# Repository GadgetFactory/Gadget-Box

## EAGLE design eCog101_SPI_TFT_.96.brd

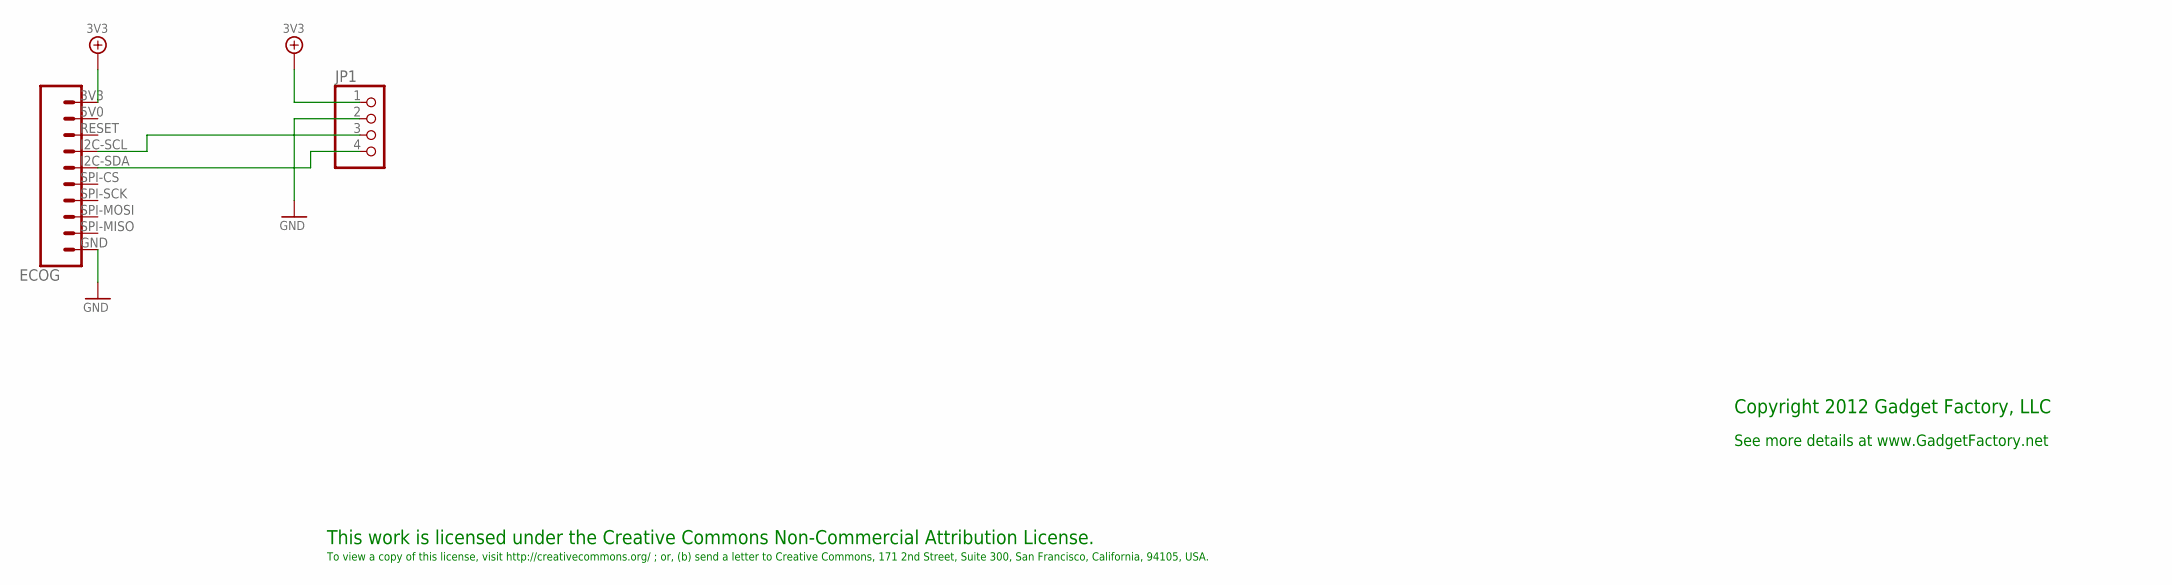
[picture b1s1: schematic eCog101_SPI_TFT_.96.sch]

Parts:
ECOG: ECOG_BUSES_ROWECOG_BUSES_SMD; ECOG_BUSES_SMD
JP1: PINHD-1X4; 1X04

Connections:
3V3: ECOG.3V3, JP1.1
GND: ECOG.GND, JP1.2
unnamed: ECOG.I2C-SCL, JP1.3
unnamed: ECOG.I2C-SDA, JP1.4

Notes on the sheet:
This work is licensed under the Creative Commons Non-Commercial Attribution License.
To view a copy of this license, visit http://creativecommons.org/ ; or, (b) send a letter to Creative Commons, 171 2nd Street, Suite 300, San Francisco, California, 94105, USA.
Copyright 2012 Gadget Factory, LLC
See more details at www.GadgetFactory.net

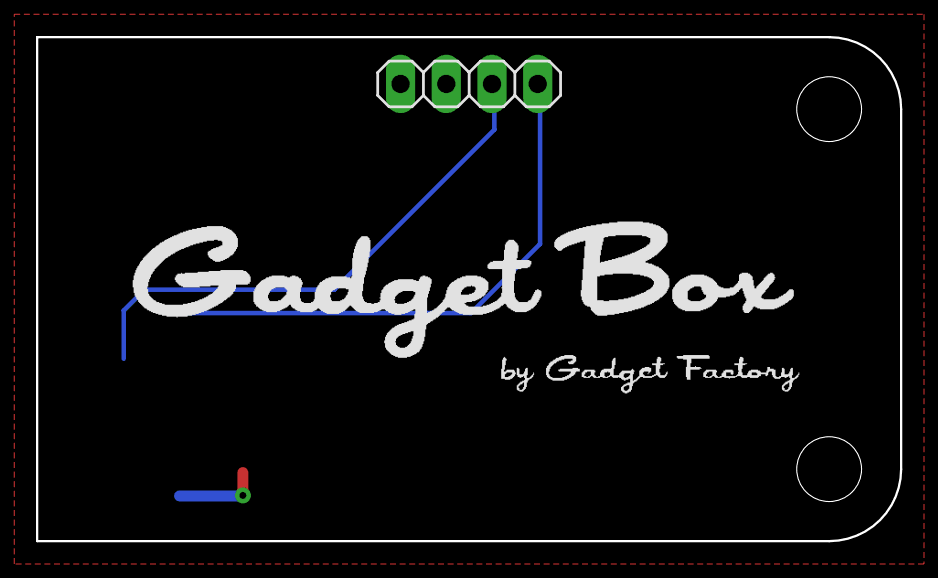
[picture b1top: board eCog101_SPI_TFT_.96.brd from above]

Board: 2 copper layers, 48.0 x 28.0 mm, 3 parts (0 on the bottom side), 4 nets.

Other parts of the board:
U$1: GADGETBOX_TEXT

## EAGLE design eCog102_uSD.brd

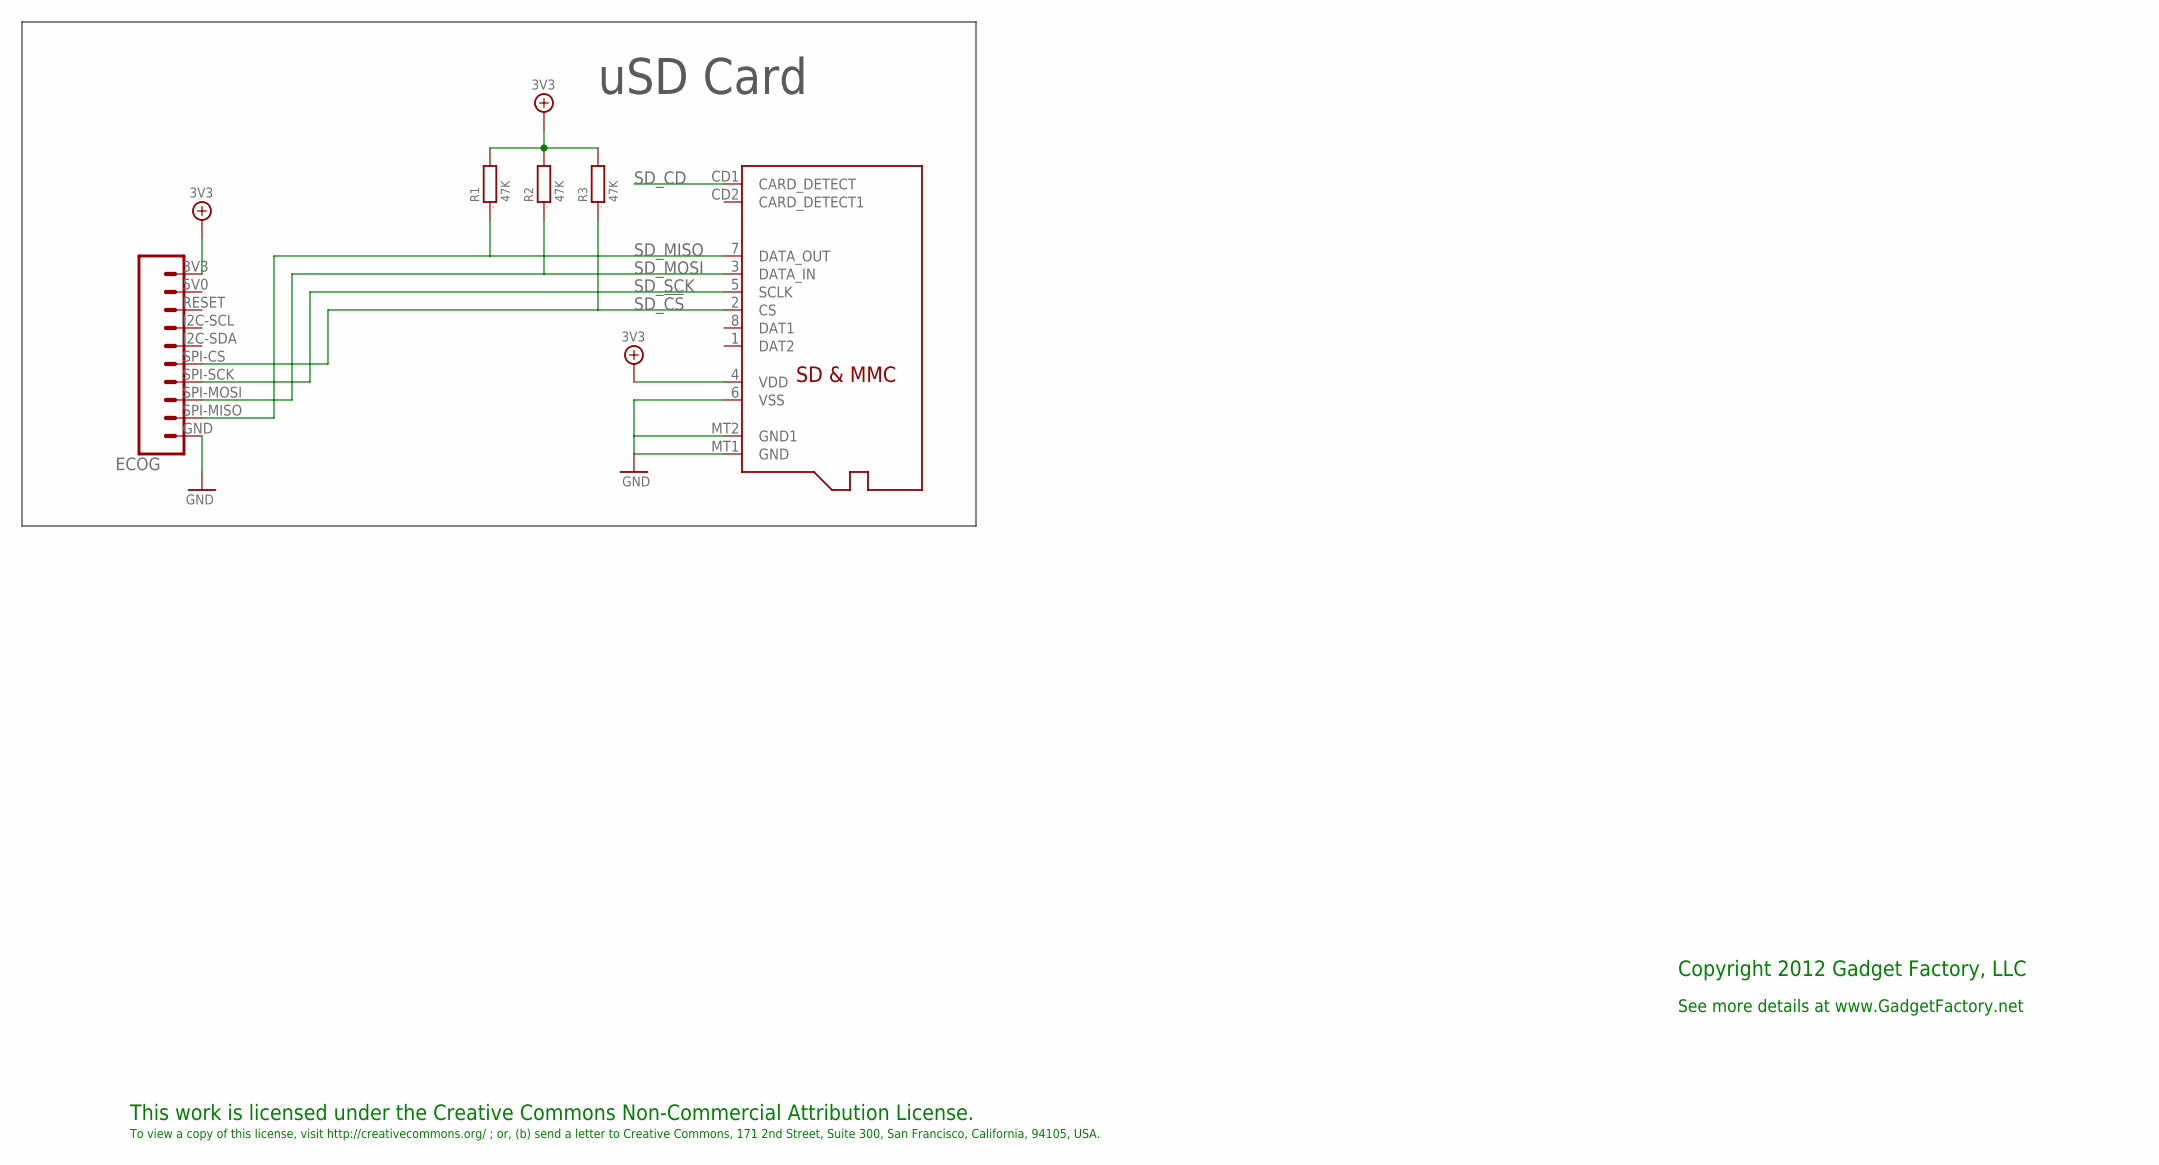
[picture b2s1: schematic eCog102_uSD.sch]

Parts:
ECOG: ECOG_BUSES_ROWECOG_BUSES_SMD; ECOG_BUSES_SMD
R1, R2, R3: 47K; 0805; PARTNO RMCF0805JT47K0; DIGIKEY RMCF0805JT47K0CT-ND
SD1: MICROSD; PARTNO 101-00660-68-6; DIGIKEY 101-00660-68-6-1-ND

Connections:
3V3: ECOG.3V3, R1.2, R2.2, R3.2, SD1.4 (VDD)
GND: ECOG.GND, SD1.6 (VSS), SD1.MT1 (GND), SD1.MT2 (GND1)
SD_!CS: ECOG.SPI-CS, R3.1, SD1.2 (CS)
SD_CD: SD1.CD1 (CARD_DETECT)
SD_MISO: ECOG.SPI-MISO, R1.1, SD1.7 (DATA_OUT)
SD_MOSI: ECOG.SPI-MOSI, R2.1, SD1.3 (DATA_IN)
SD_SCK: ECOG.SPI-SCK, SD1.5 (SCLK)

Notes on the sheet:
This work is licensed under the Creative Commons Non-Commercial Attribution License.
To view a copy of this license, visit http://creativecommons.org/ ; or, (b) send a letter to Creative Commons, 171 2nd Street, Suite 300, San Francisco, California, 94105, USA.
Copyright 2012 Gadget Factory, LLC
See more details at www.GadgetFactory.net
uSD Card

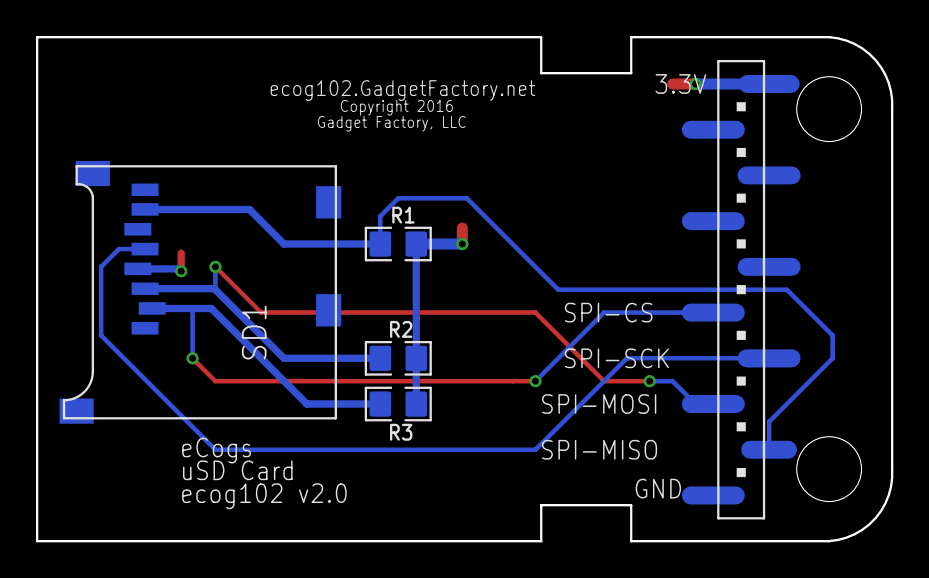
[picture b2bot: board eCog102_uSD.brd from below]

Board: 2 copper layers, 47.5 x 28.0 mm, 7 parts (4 on the bottom side), 6 nets.

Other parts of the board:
U$1: GADGETBOX_TEXT
U$2: OSHW_FILLX200_NOTEXT

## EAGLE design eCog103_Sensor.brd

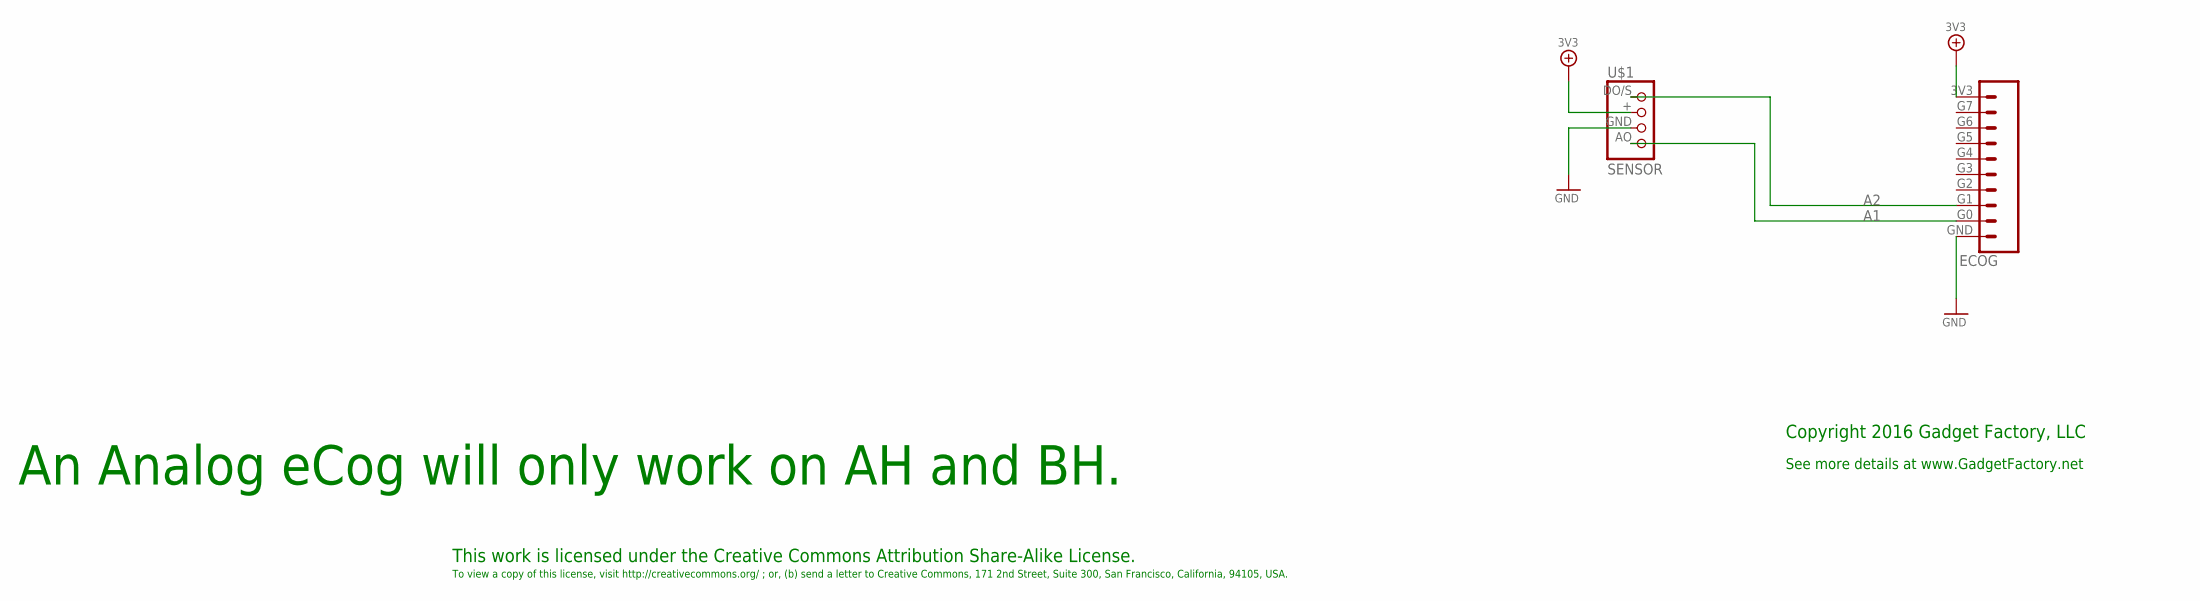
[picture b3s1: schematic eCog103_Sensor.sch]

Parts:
ECOG: ECOG_GENERAL_ROWECOG_GENERAL_SMD; ECOG_GENERAL_SMD
U$1: SENSOR; SENSOR-HJX4

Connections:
3V3: ECOG.3V3, U$1.+
A1: ECOG.G0, U$1.AO
A2: ECOG.G1, U$1.DO/S
GND: ECOG.GND, U$1.GND

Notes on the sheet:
This work is licensed under the Creative Commons Attribution Share-Alike License.
To view a copy of this license, visit http://creativecommons.org/ ; or, (b) send a letter to Creative Commons, 171 2nd Street, Suite 300, San Francisco, California, 94105, USA.
Copyright 2016 Gadget Factory, LLC
See more details at www.GadgetFactory.net
An Analog eCog will only work on AH and BH.

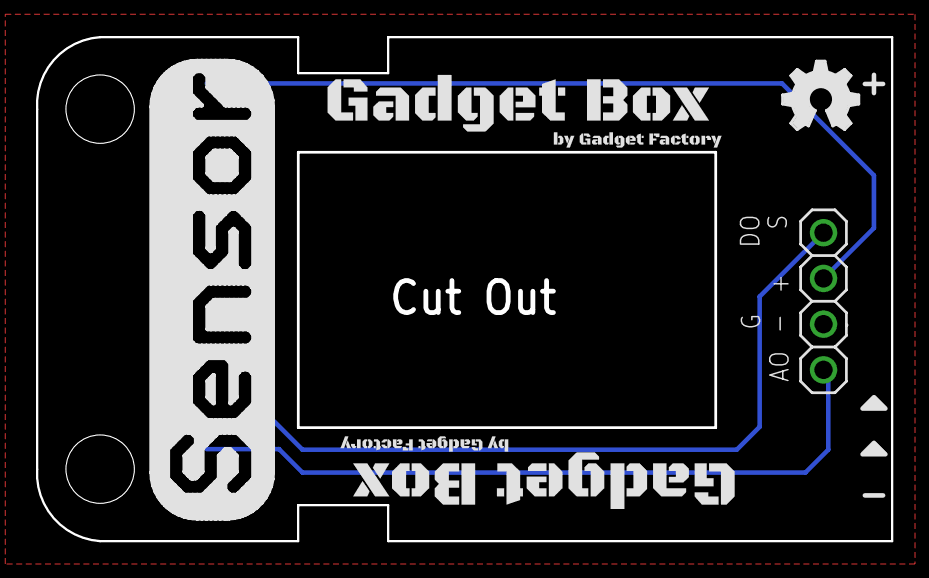
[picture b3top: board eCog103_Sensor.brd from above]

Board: 2 copper layers, 47.5 x 28.0 mm, 7 parts (0 on the bottom side), 4 nets.

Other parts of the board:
U$2, U$3: LEGEND_ANALOG
U$4, U$6: GADGETBOX_SMALL
U$5: OSHW_FILLX150_NOTEXT

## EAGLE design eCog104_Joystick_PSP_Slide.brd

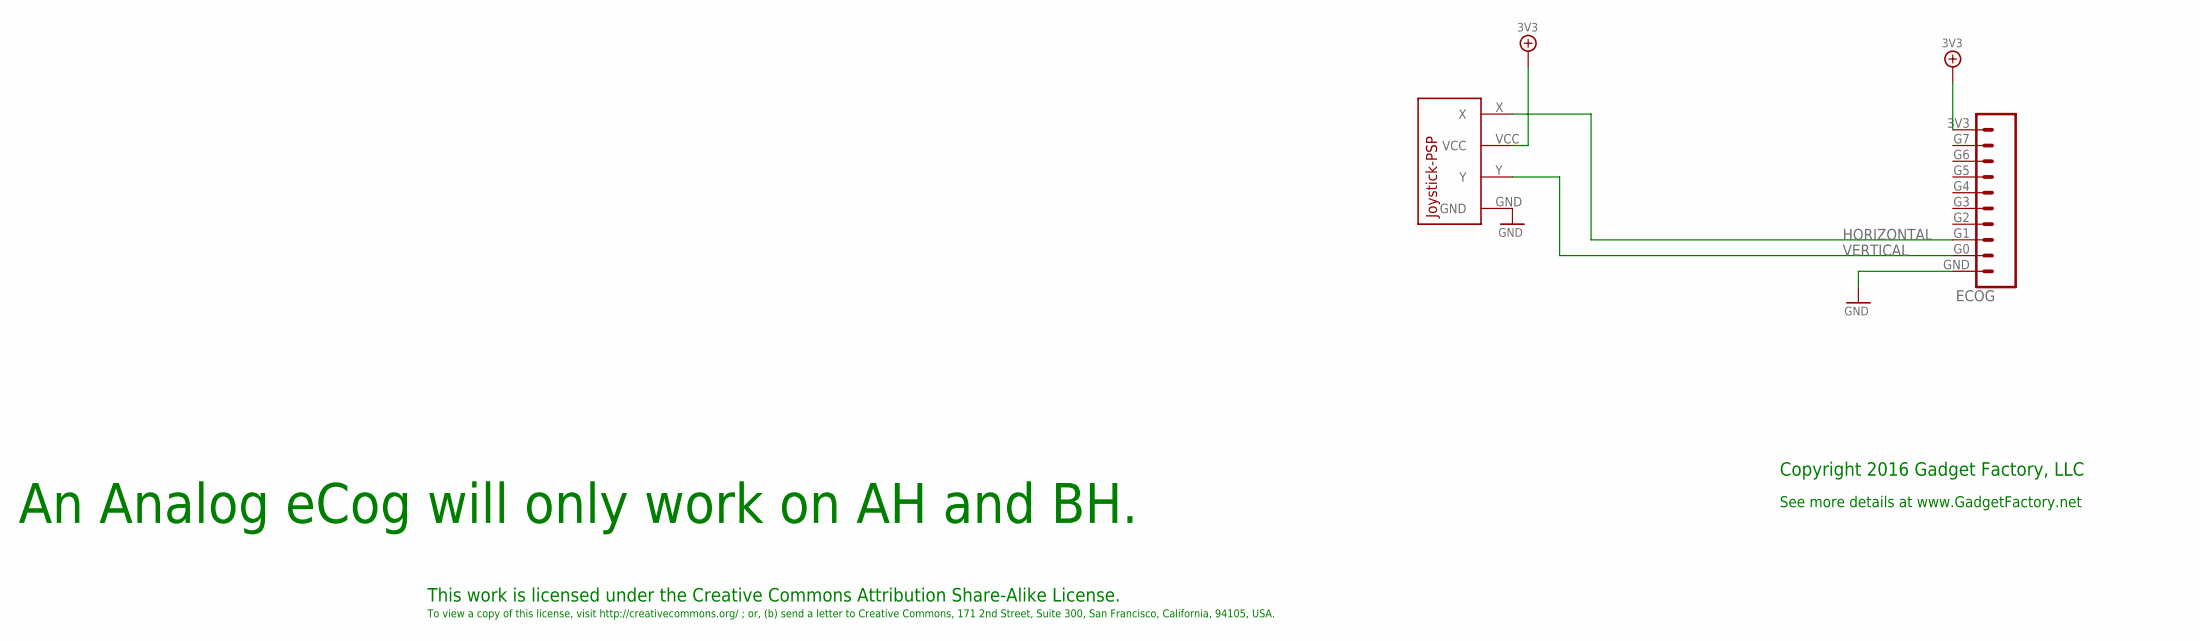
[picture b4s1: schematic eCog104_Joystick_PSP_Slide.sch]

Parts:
ECOG: ECOG_GENERAL_ROWECOG_GENERAL_SMD; ECOG_GENERAL_SMD
U$4: JOYSTICK-PSP1000

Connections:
3V3: ECOG.3V3, U$4.VCC
GND: ECOG.GND, U$4.GND
HORIZONTAL: ECOG.G1, U$4.X
VERTICAL: ECOG.G0, U$4.Y

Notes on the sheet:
This work is licensed under the Creative Commons Attribution Share-Alike License.
To view a copy of this license, visit http://creativecommons.org/ ; or, (b) send a letter to Creative Commons, 171 2nd Street, Suite 300, San Francisco, California, 94105, USA.
Copyright 2016 Gadget Factory, LLC
See more details at www.GadgetFactory.net
An Analog eCog will only work on AH and BH.

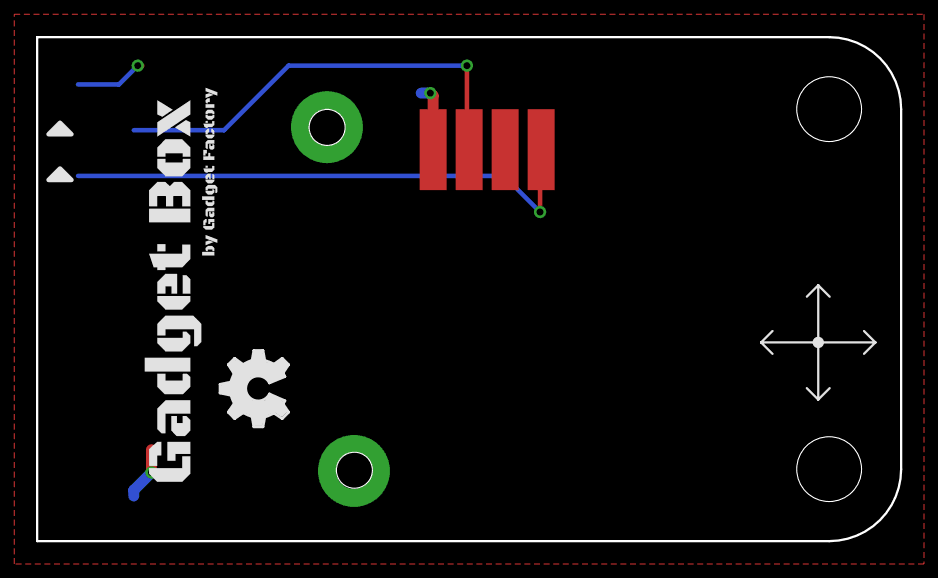
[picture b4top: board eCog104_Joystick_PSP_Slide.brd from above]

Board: 2 copper layers, 48.0 x 28.0 mm, 6 parts (0 on the bottom side), 4 nets.

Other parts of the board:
U$1, U$2: LEGEND_ANALOG
U$3: GADGETBOX_SMALL
U$5: OSHW_FILLX150_NOTEXT

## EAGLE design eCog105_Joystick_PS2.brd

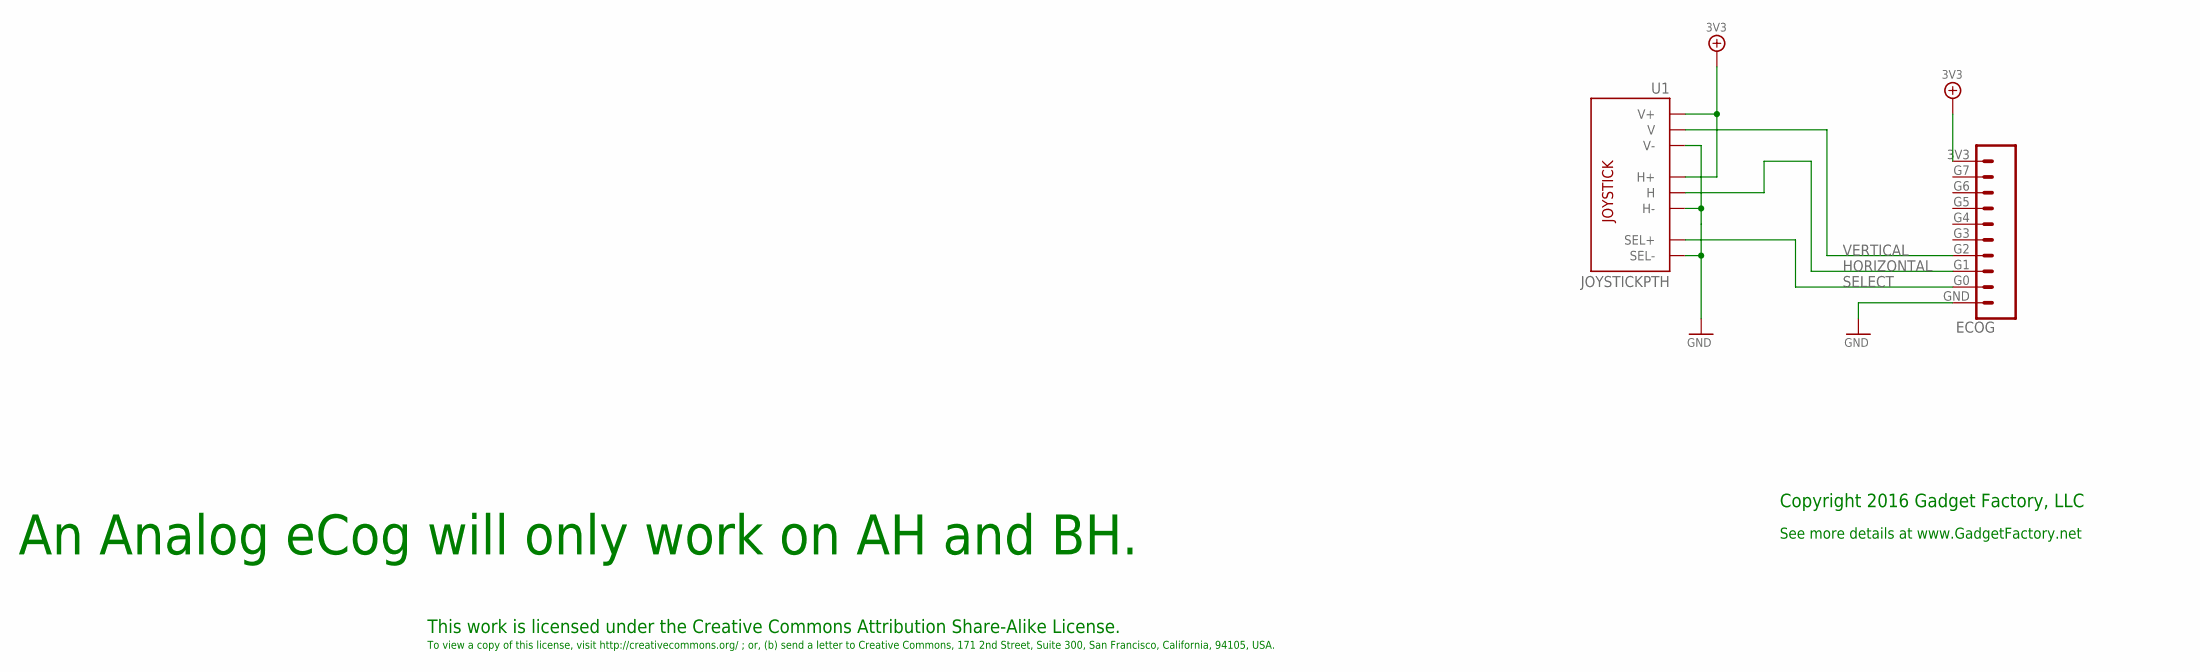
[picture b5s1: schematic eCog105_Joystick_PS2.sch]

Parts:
ECOG: ECOG_GENERAL_ROWECOG_GENERAL_SMD; ECOG_GENERAL_SMD
U1: JOYSTICKPTH; JOYSTICK

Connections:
3V3: ECOG.3V3, U1.H1 (H+), U1.V1 (V+)
GND: ECOG.GND, U1.B2A (SEL-), U1.H3 (H-), U1.V3 (V-)
HORIZONTAL: ECOG.G1, U1.H2 (H)
SELECT: ECOG.G0, U1.B1A (SEL+)
VERTICAL: ECOG.G2, U1.V2 (V)

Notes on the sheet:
This work is licensed under the Creative Commons Attribution Share-Alike License.
To view a copy of this license, visit http://creativecommons.org/ ; or, (b) send a letter to Creative Commons, 171 2nd Street, Suite 300, San Francisco, California, 94105, USA.
Copyright 2016 Gadget Factory, LLC
See more details at www.GadgetFactory.net
An Analog eCog will only work on AH and BH.

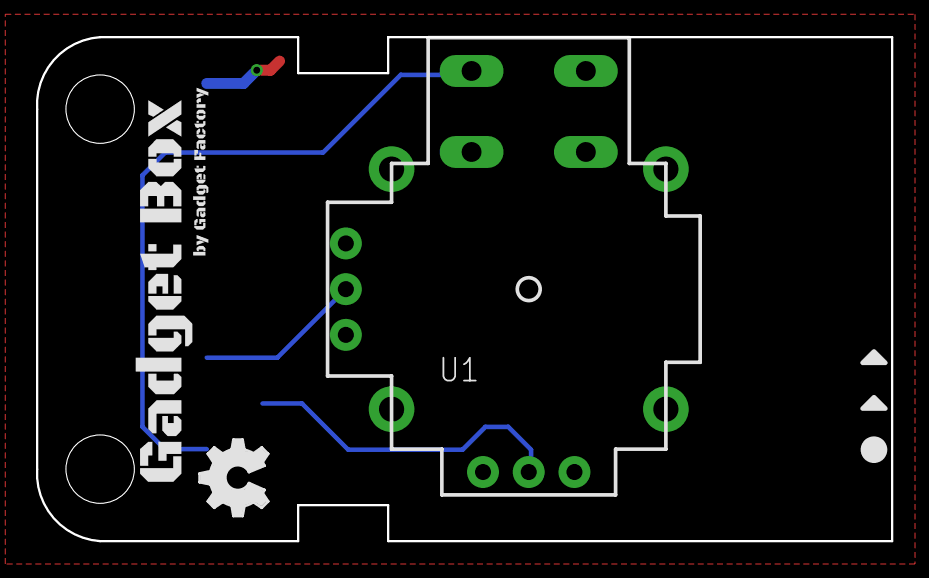
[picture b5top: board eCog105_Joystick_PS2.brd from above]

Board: 2 copper layers, 47.5 x 28.0 mm, 7 parts (0 on the bottom side), 5 nets.

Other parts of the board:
U$1, U$2: LEGEND_ANALOG
U$3: LEGEND_DIO
U$4: GADGETBOX_SMALL
U$5: OSHW_FILLX150_NOTEXT

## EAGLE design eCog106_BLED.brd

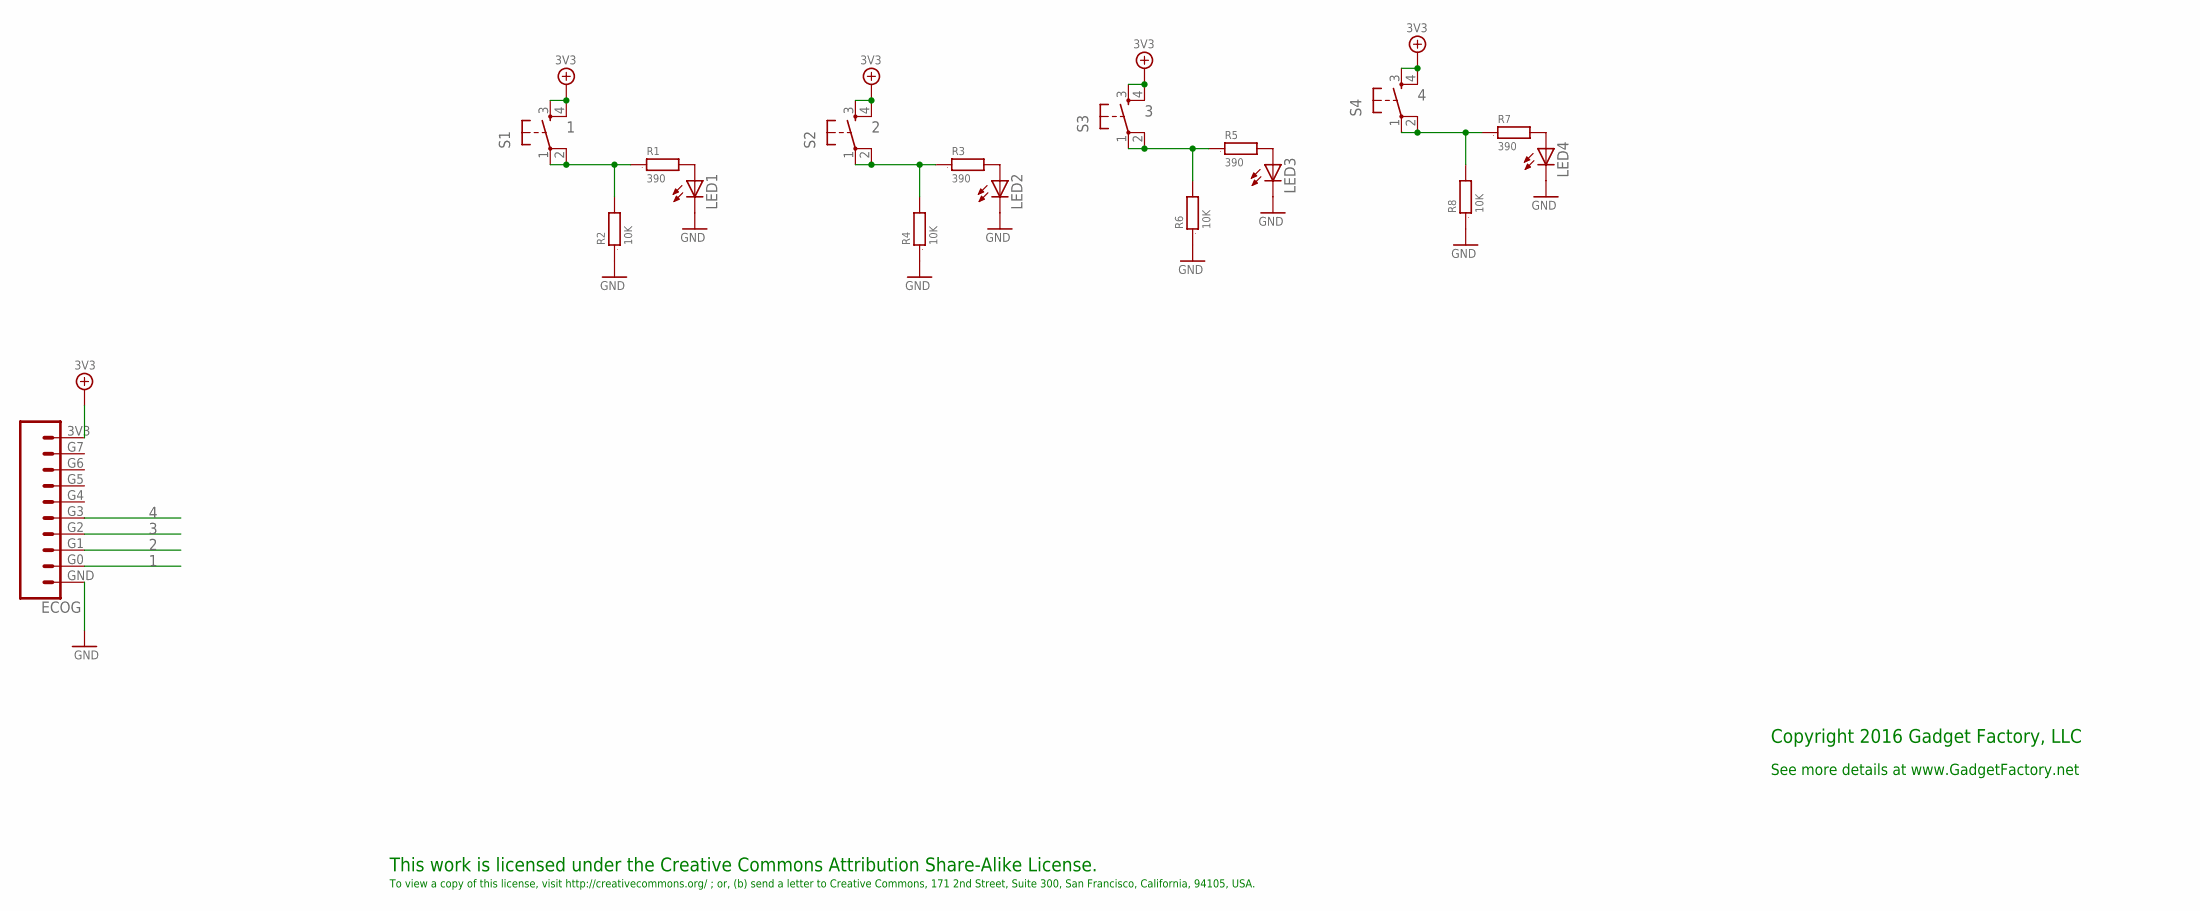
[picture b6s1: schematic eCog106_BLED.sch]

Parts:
ECOG: ECOG_GENERAL_ROWECOG_GENERAL_SMD; ECOG_GENERAL_SMD
LED1, LED2, LED3, LED4: LEDCHIP-LED0805; CHIP-LED0805; DIGIKEY 475-1410-2-ND
R1, R3, R5, R7: 390; 0805; DIGIKEY RMCF0805JT390RCT-ND
R2, R4, R6, R8: 10K; 0805; DIGIKEY RMCF0805JT10K0CT-ND
S1, S2, S3, S4: TAC_SWITCHPTH; TACTILE-PTH; DIGIKEY 679-2428-ND

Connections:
1: ECOG.G0, R1.1, R2.2, S1.1, S1.2
2: ECOG.G1, R3.1, R4.2, S2.1, S2.2
3: ECOG.G2, R5.1, R6.2, S3.1, S3.2
3V3: ECOG.3V3, S1.3, S1.4, S2.3, S2.4, S3.3, S3.4, S4.3, S4.4
4: ECOG.G3, R7.1, R8.2, S4.1, S4.2
GND: ECOG.GND, LED1.C, LED2.C, LED3.C, LED4.C, R2.1, R4.1, R6.1, R8.1
unnamed: LED1.A, R1.2
unnamed: LED2.A, R3.2
unnamed: LED3.A, R5.2
unnamed: LED4.A, R7.2

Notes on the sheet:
This work is licensed under the Creative Commons Attribution Share-Alike License.
To view a copy of this license, visit http://creativecommons.org/ ; or, (b) send a letter to Creative Commons, 171 2nd Street, Suite 300, San Francisco, California, 94105, USA.
Copyright 2016 Gadget Factory, LLC
See more details at www.GadgetFactory.net

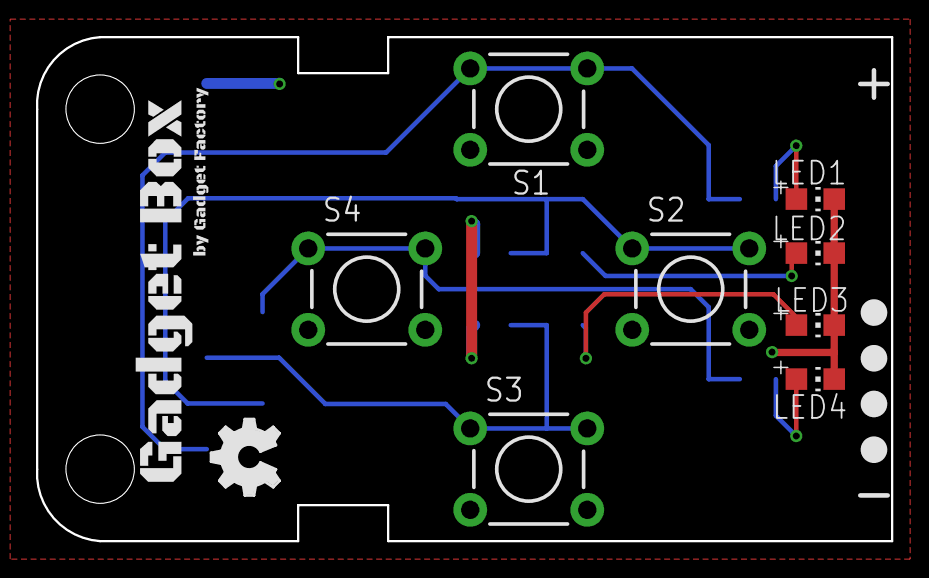
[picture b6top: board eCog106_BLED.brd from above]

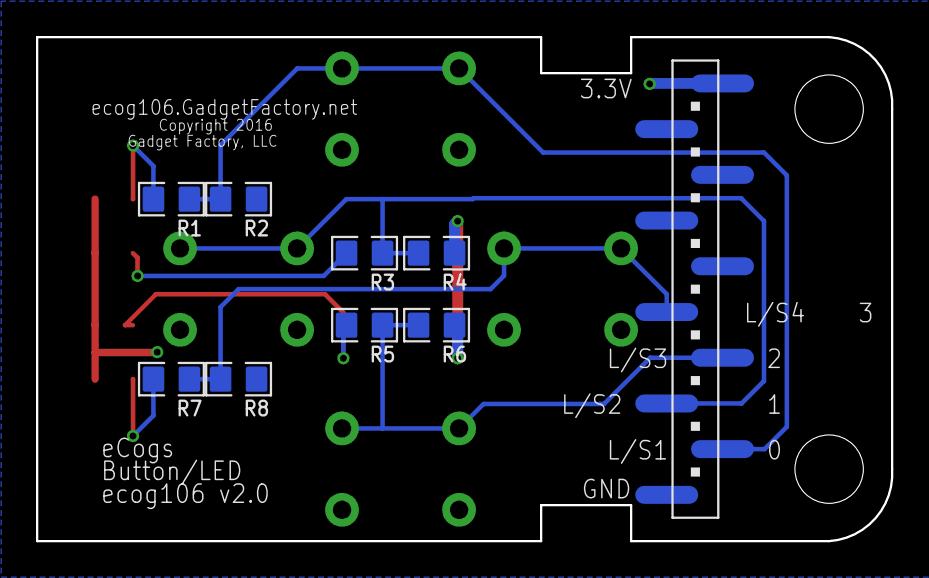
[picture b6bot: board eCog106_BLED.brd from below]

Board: 2 copper layers, 47.5 x 28.0 mm, 23 parts (8 on the bottom side), 10 nets.

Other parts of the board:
U$1, U$2, U$3, U$4: LEGEND_DIO
U$5: GADGETBOX_SMALL
U$6: OSHW_FILLX150_NOTEXT

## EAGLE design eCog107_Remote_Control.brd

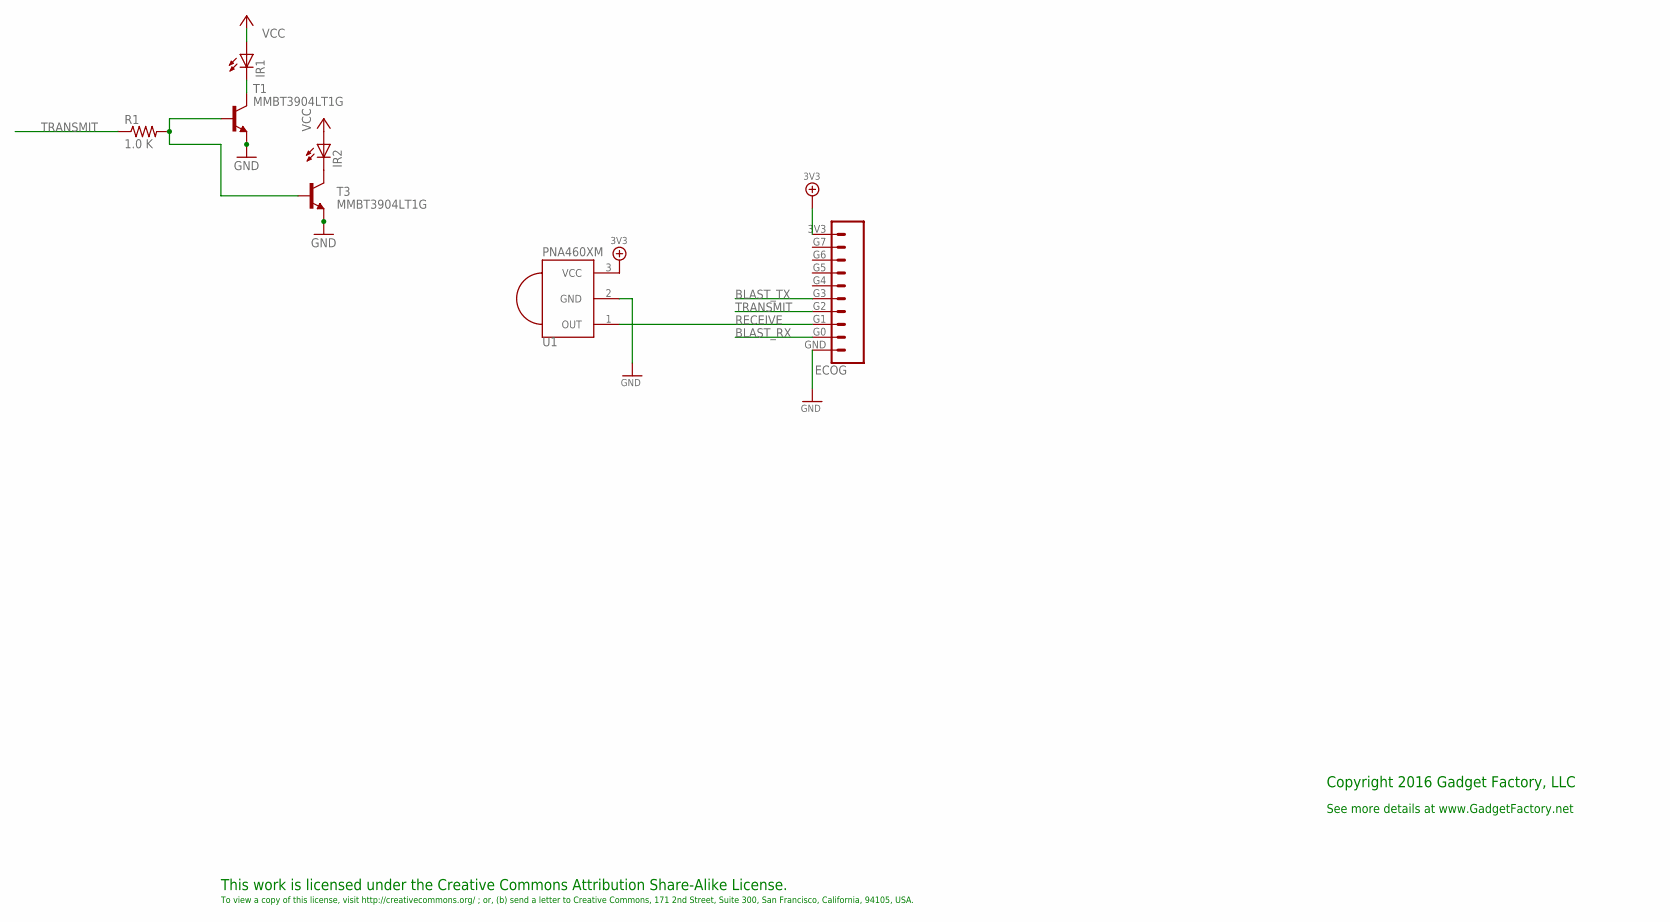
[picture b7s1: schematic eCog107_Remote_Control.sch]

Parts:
ECOG: ECOG_GENERAL_ROWECOG_GENERAL_SMD; ECOG_GENERAL_SMD
IR1: LED5MM; DIGIKEY 1080-1082-ND
IR2: LED5MM; DIGIKEY 1080-1080-ND
R1: 1.0 K; R0805; DIGIKEY 311-1.0KARCT-ND
T1, T3: MMBT3904LT1G; SOT23-BEC; DIGIKEY MMBT3904LT1GOSCT-ND
U1: PNA460XM; DIGIKEY 751-1227-ND

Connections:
3V3: ECOG.3V3, IR1.A, IR2.A, U1.3 (VCC)
BLAST_RX: ECOG.G0
BLAST_TX: ECOG.G3
GND: ECOG.GND, T1.E, T3.E, U1.2 (GND)
unnamed: IR1.K (C), T1.C
unnamed: IR2.K (C), T3.C
unnamed: R1.2, T1.B, T3.B
RECEIVE: ECOG.G1, U1.1 (OUT)
TRANSMIT: ECOG.G2, R1.1

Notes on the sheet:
This work is licensed under the Creative Commons Attribution Share-Alike License.
To view a copy of this license, visit http://creativecommons.org/ ; or, (b) send a letter to Creative Commons, 171 2nd Street, Suite 300, San Francisco, California, 94105, USA.
Copyright 2016 Gadget Factory, LLC
See more details at www.GadgetFactory.net

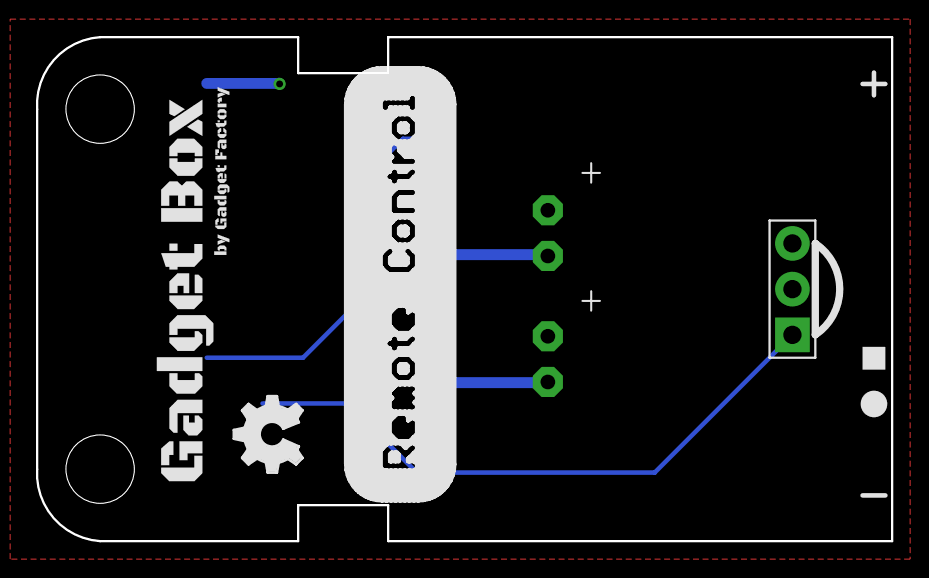
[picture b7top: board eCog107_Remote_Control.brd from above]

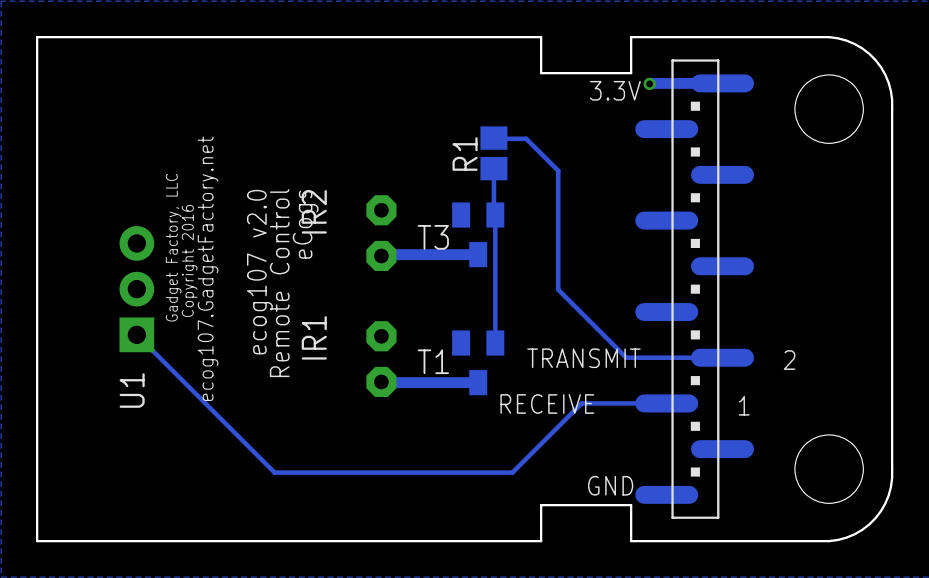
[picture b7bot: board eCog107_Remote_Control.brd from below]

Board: 2 copper layers, 47.5 x 28.0 mm, 11 parts (3 on the bottom side), 7 nets.

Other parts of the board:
U$2: LEGEND_PWM
U$4: LEGEND_DIO
U$5: GADGETBOX_SMALL
U$6: OSHW_FILLX150_NOTEXT

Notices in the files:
parts and their libraries:
SparkFun: Licensing: CC v3.0 Share-Alike You are welcome to use this library for commercial purposes.
